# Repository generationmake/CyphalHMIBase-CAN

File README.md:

# CyphalHMIBase-CAN
HMI Board for the Raspberry Pi Pico with a display and some knobs to connect via CAN using OpenCyphal and UCANPHY Micro

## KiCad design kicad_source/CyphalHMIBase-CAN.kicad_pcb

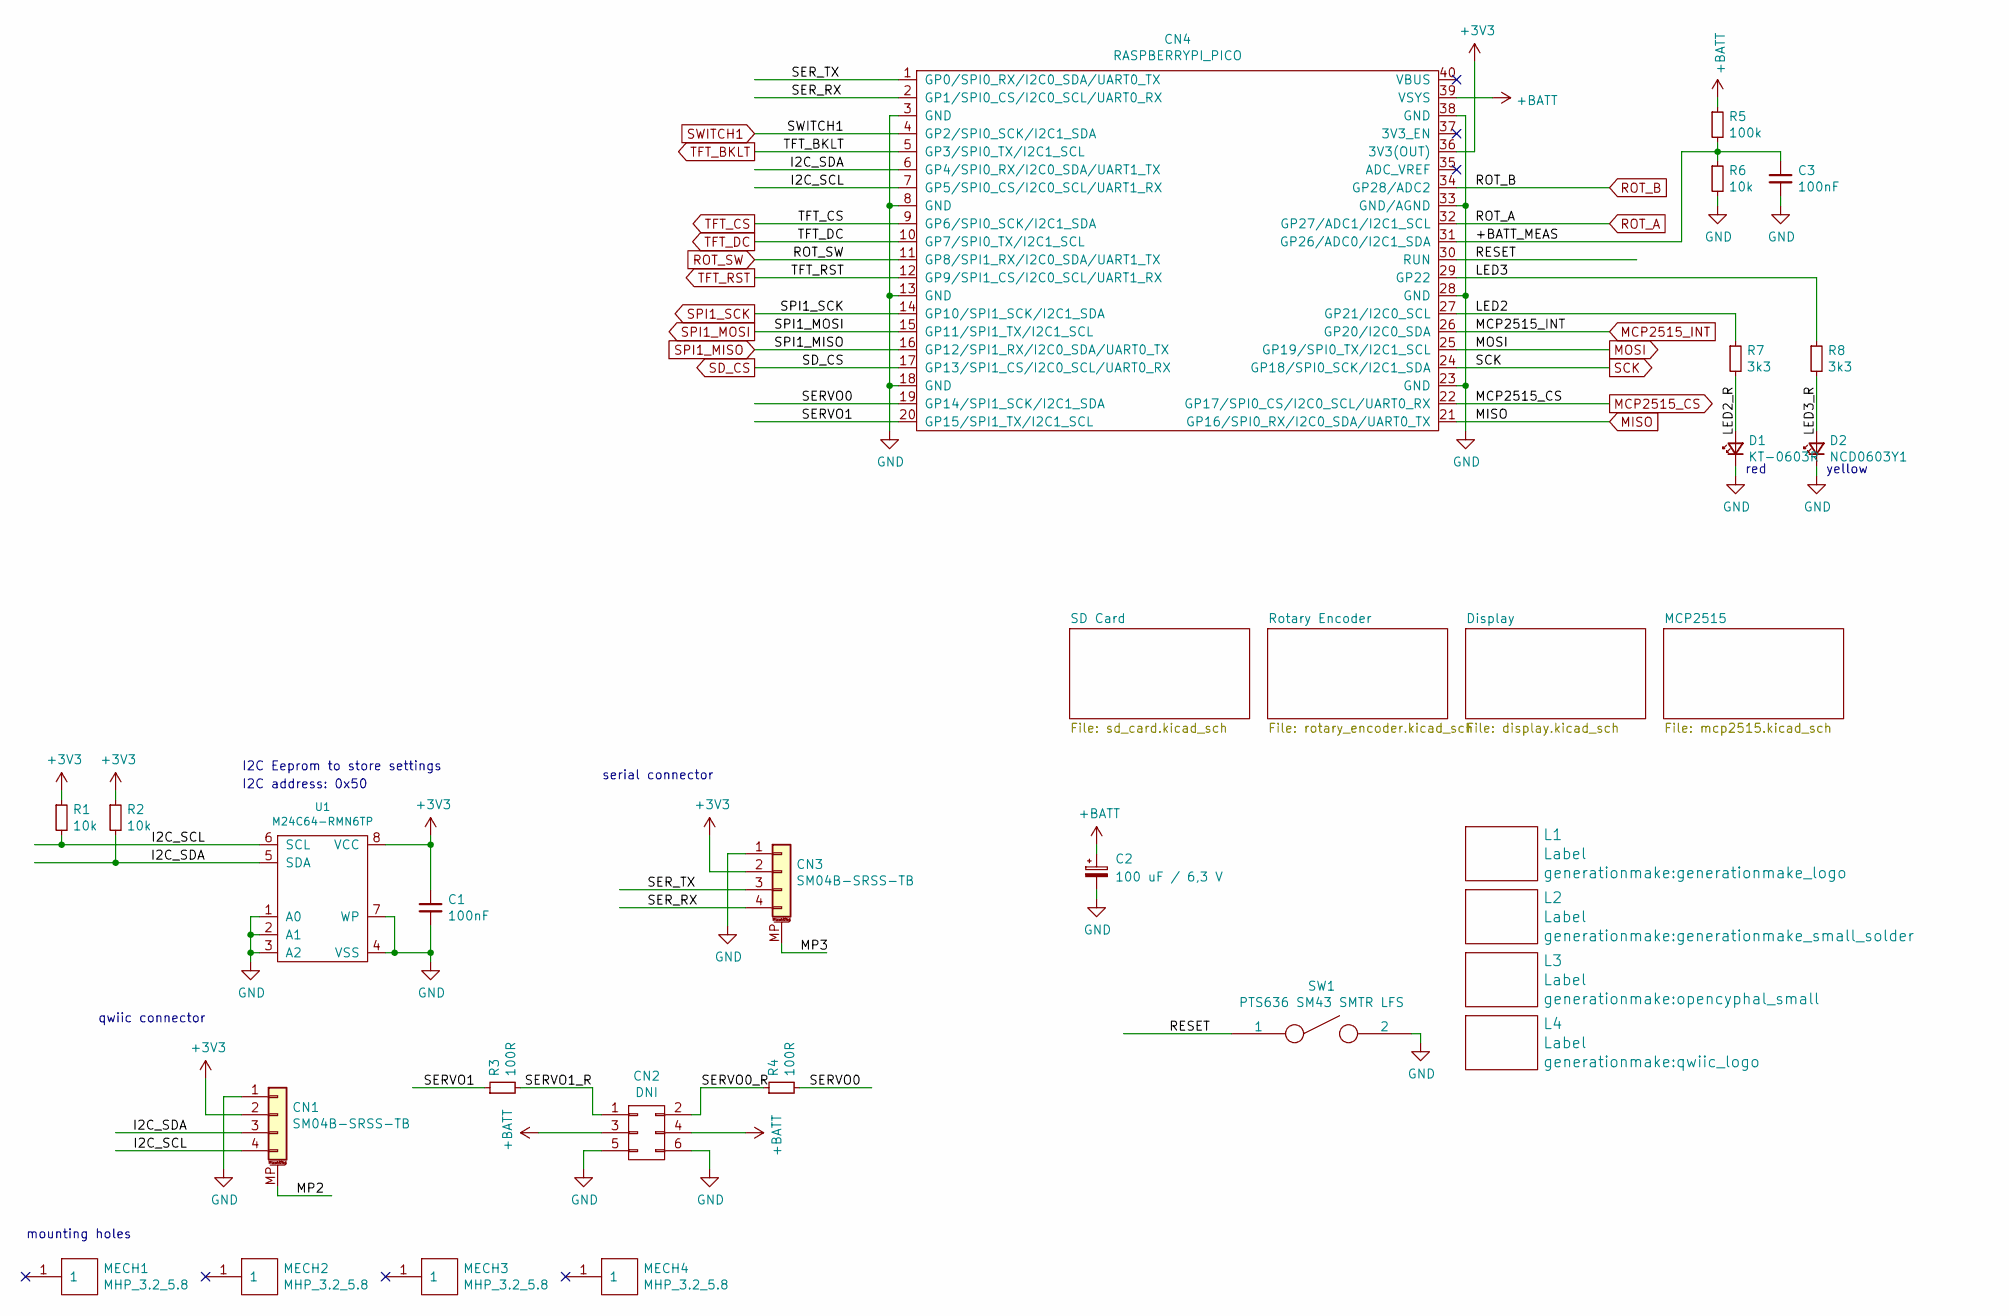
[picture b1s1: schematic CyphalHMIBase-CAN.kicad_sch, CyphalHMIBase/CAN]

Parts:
C1, C3: 100nF; C_0603_1608Metric; LCSC C14663
C2: 100 uF / 6,3 V; CP_Elec_5x5.3; LCSC C3001204
CN1, CN3: SM04B-SRSS-TB; JST_SH_SM04B-SRSS-TB_1x04-1MP_P1.00mm_Horizontal; LCSC C160404
CN2: DNI; PinHeader_2x03_P2.54mm_Horizontal
CN4: RASPBERRYPI_PICO; RASPI_PICO_SOLDER_ONLY
D1: KT-0603R; LED_0603_1608Metric; LCSC C2286
D2: NCD0603Y1; LED_0603_1608Metric; LCSC C84268
L1: Label; generationmake_logo
L2: Label; generationmake_small_solder
L3: Label; opencyphal_small
L4: Label; qwiic_logo
MECH1, MECH2, MECH3, MECH4: MHP_3.2_5.8
R1, R2, R6: 10k; R_0603_1608Metric; LCSC C25804
R3, R4: 100R; R_0603_1608Metric; LCSC C22775
R5: 100k; R_0603_1608Metric; LCSC C25803
R7, R8: 3k3; R_0603_1608Metric; LCSC C22978
SW1: PTS636 SM43 SMTR LFS; SW_SPST_CK_RS282G05A3; LCSC C2800965
U1: M24C64-RMN6TP; SOIC-8_3.9x4.9mm_P1.27mm; LCSC C79988

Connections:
+3V3: C1.1, CN1.2, CN3.2, CN4.36 (3V3(OUT)), R1.1, R2.1, U1.8 (VCC); also elsewhere on the board
+BATT: C2.1, CN2.3, CN2.4, CN4.39 (VSYS), R5.1; also elsewhere on the board
/+BATT_MEAS: C3.1, CN4.31 (GP26/ADC0/I2C1_SDA), R5.2, R6.1
/I2C_SCL: CN1.4, CN4.7 (GP5/SPI0_CS/I2C0_SCL/UART1_RX), R1.2, U1.6 (SCL)
/I2C_SDA: CN1.3, CN4.6 (GP4/SPI0_RX/I2C0_SDA/UART1_TX), R2.2, U1.5 (SDA)
/LED2: CN4.27 (GP21/I2C0_SCL), R7.1
/LED2_R: D1.2 (A), R7.2
/LED3: CN4.29 (GP22), R8.1
/LED3_R: D2.2 (A), R8.2
/MP2: CN1.MP (MountPin)
/MP3: CN3.MP (MountPin)
/RESET: CN4.30 (RUN), SW1.1
/SERVO0: CN4.19 (GP14/SPI1_SCK/I2C1_SDA), R4.2
/SERVO0_R: CN2.2, R4.1
/SERVO1: CN4.20 (GP15/SPI1_TX/I2C1_SCL), R3.1
/SERVO1_R: CN2.1, R3.2
/SER_RX: CN3.4, CN4.2 (GP1/SPI0_CS/I2C0_SCL/UART0_RX)
/SER_TX: CN3.3, CN4.1 (GP0/SPI0_RX/I2C0_SDA/UART0_TX)
GND: C1.2, C2.2, C3.2, CN1.1, CN2.5, CN2.6, CN3.1, CN4.3 (GND), CN4.8 (GND), CN4.13 (GND), CN4.18 (GND), CN4.23 (GND), CN4.28 (GND), CN4.33 (GND/AGND), CN4.38 (GND), D1.1 (K), D2.1 (K), R6.2, SW1.2, U1.1 (A0), U1.2 (A1), U1.3 (A2), U1.4 (VSS), U1.7 (WP); also elsewhere on the board
MCP2515_CS: CN4.22 (GP17/SPI0_CS/I2C0_SCL/UART0_RX); also elsewhere on the board
MCP2515_INT: CN4.26 (GP20/I2C0_SDA); also elsewhere on the board
MISO: CN4.21 (GP16/SPI0_RX/I2C0_SDA/UART0_TX); also elsewhere on the board
MOSI: CN4.25 (GP19/SPI0_TX/I2C1_SCL); also elsewhere on the board
ROT_A: CN4.32 (GP27/ADC1/I2C1_SCL); also elsewhere on the board
ROT_B: CN4.34 (GP28/ADC2); also elsewhere on the board
ROT_SW: CN4.11 (GP8/SPI1_RX/I2C0_SDA/UART1_TX); also elsewhere on the board
SCK: CN4.24 (GP18/SPI0_SCK/I2C1_SDA); also elsewhere on the board
SD_CS: CN4.17 (GP13/SPI1_CS/I2C0_SCL/UART0_RX); also elsewhere on the board
SPI1_MISO: CN4.16 (GP12/SPI1_RX/I2C0_SDA/UART0_TX); also elsewhere on the board
SPI1_MOSI: CN4.15 (GP11/SPI1_TX/I2C1_SCL); also elsewhere on the board
SPI1_SCK: CN4.14 (GP10/SPI1_SCK/I2C1_SDA); also elsewhere on the board
SWITCH1: CN4.4 (GP2/SPI0_SCK/I2C1_SDA); also elsewhere on the board
TFT_BKLT: CN4.5 (GP3/SPI0_TX/I2C1_SCL); also elsewhere on the board
TFT_CS: CN4.9 (GP6/SPI0_SCK/I2C1_SDA); also elsewhere on the board
TFT_DC: CN4.10 (GP7/SPI0_TX/I2C1_SCL); also elsewhere on the board
TFT_RST: CN4.12 (GP9/SPI1_CS/I2C0_SCL/UART1_RX); also elsewhere on the board

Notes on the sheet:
yellow
serial connector
qwiic connector
mounting holes
red
I2C address: 0x50
I2C Eeprom to store settings

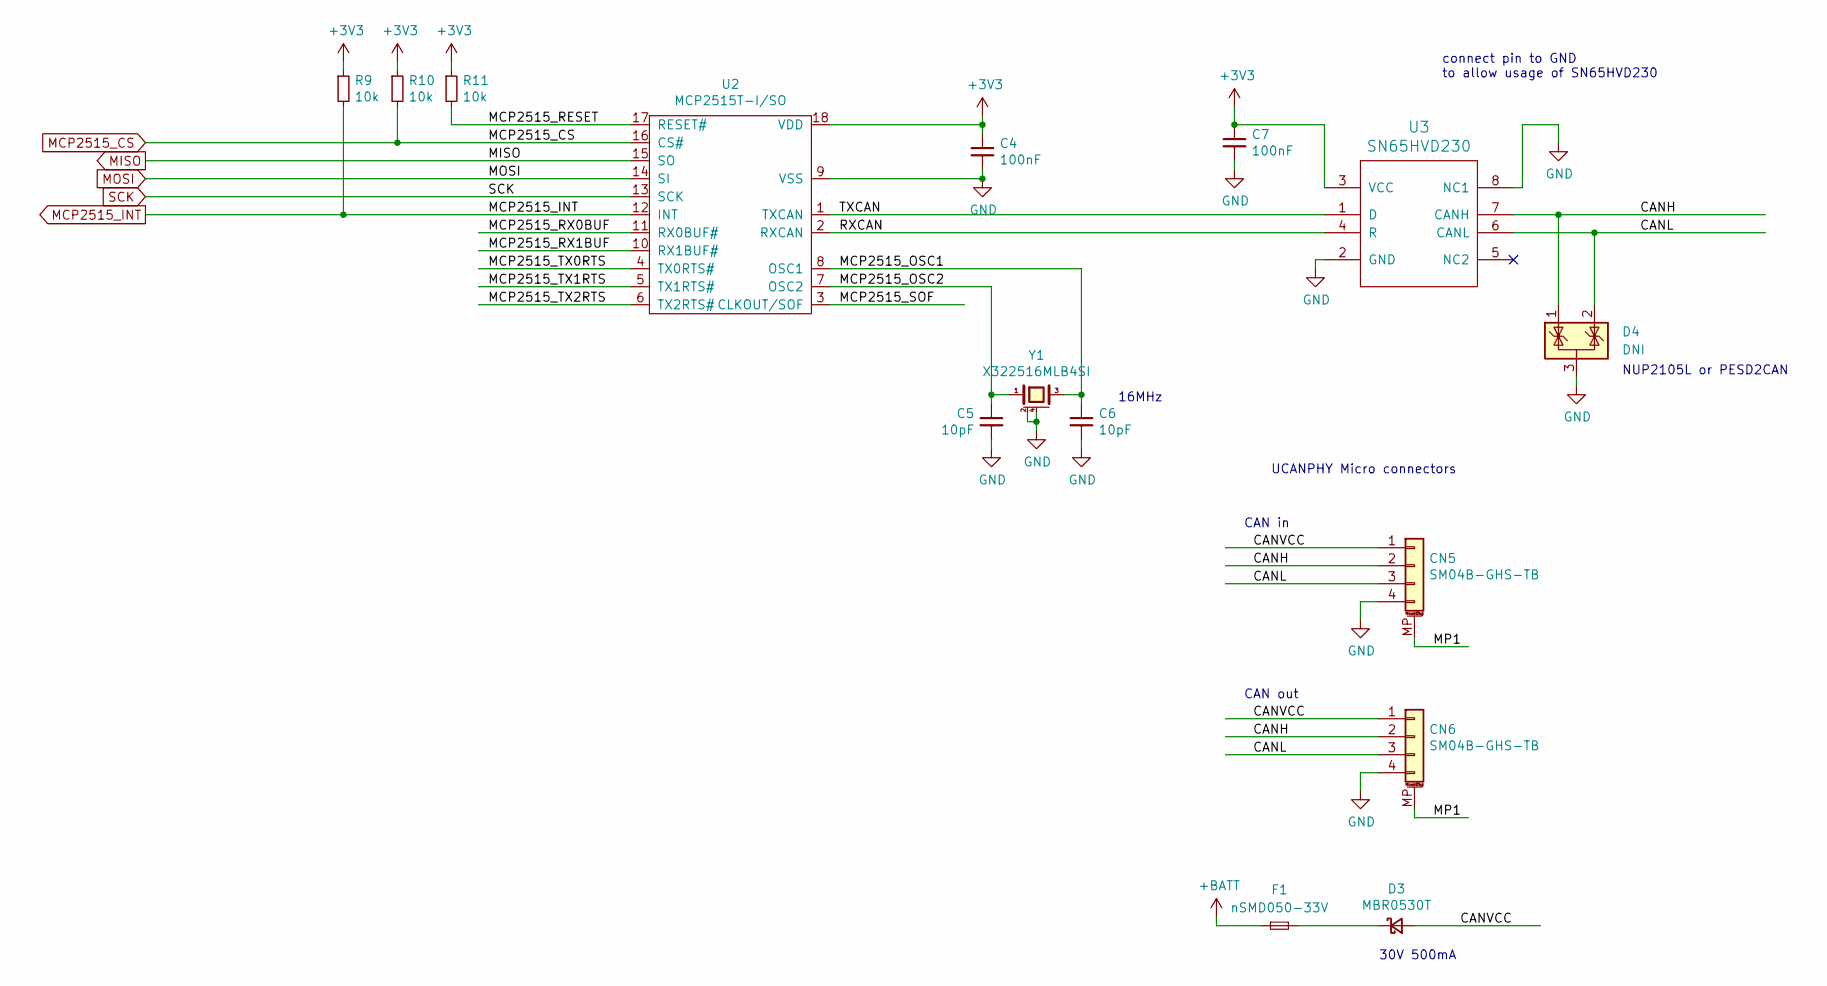
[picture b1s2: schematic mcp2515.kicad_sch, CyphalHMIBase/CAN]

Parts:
C4, C7: 100nF; C_0603_1608Metric; LCSC C14663
C5, C6: 10pF; C_0603_1608Metric; LCSC C1634
CN5, CN6: SM04B-GHS-TB; JST_GH_SM04B-GHS-TB_1x04-1MP_P1.25mm_Horizontal; LCSC C189895
D3: MBR0530T; D_SOD-123; LCSC C77336
D4: DNI; SOT-23
F1: nSMD050-33V; Fuse_1206_3216Metric; LCSC C70077
R9, R10, R11: 10k; R_0603_1608Metric; LCSC C25804
U2: MCP2515T-I/SO; SOIC-18W_7.5x11.6mm_P1.27mm; LCSC C153782
U3: SN65HVD230; SOIC-8_3.9x4.9mm_P1.27mm; LCSC C12084
Y1: X322516MLB4SI; Crystal_SMD_3.2x2.5mm_4Pad; LCSC C13738

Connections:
+3V3: C4.1, C7.1, R9.1, R10.1, R11.1, U2.18 (VDD), U3.3 (VCC); also elsewhere on the board
+BATT: F1.1; also elsewhere on the board
/MCP2515/CANH: CN5.2, CN6.2, D4.1 (K), U3.7 (CANH)
/MCP2515/CANL: CN5.3, CN6.3, D4.2 (K), U3.6 (CANL)
/MCP2515/CANVCC: CN5.1, CN6.1, D3.2 (A)
/MCP2515/MCP2515_OSC1: C6.1, U2.8 (OSC1), Y1.3
/MCP2515/MCP2515_OSC2: C5.1, U2.7 (OSC2), Y1.1
/MCP2515/MCP2515_RESET: R11.2, U2.17 (RESET#)
/MCP2515/MCP2515_RX0BUF: U2.11 (RX0BUF#)
/MCP2515/MCP2515_RX1BUF: U2.10 (RX1BUF#)
/MCP2515/MCP2515_SOF: U2.3 (CLKOUT/SOF)
/MCP2515/MCP2515_TX0RTS: U2.4 (TX0RTS#)
/MCP2515/MCP2515_TX1RTS: U2.5 (TX1RTS#)
/MCP2515/MCP2515_TX2RTS: U2.6 (TX2RTS#)
/MCP2515/MP1: CN5.MP (MountPin), CN6.MP (MountPin)
/MCP2515/RXCAN: U2.2 (RXCAN), U3.4 (R)
/MCP2515/TXCAN: U2.1 (TXCAN), U3.1 (D)
GND: C4.2, C5.2, C6.2, C7.2, CN5.4, CN6.4, D4.3 (A), U2.9 (VSS), U3.2 (GND), U3.8 (NC1), Y1.2 (case), Y1.4 (case); also elsewhere on the board
MCP2515_CS: R10.2, U2.16 (CS#); also elsewhere on the board
MCP2515_INT: R9.2, U2.12 (INT); also elsewhere on the board
MISO: U2.15 (SO); also elsewhere on the board
MOSI: U2.14 (SI); also elsewhere on the board
unnamed: D3.1 (K), F1.2
SCK: U2.13 (SCK); also elsewhere on the board

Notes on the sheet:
16MHz
NUP2105L or PESD2CAN
connect pin to GND to allow usage of SN65HVD230
UCANPHY Micro connectors
30V 500mA
CAN in
CAN out

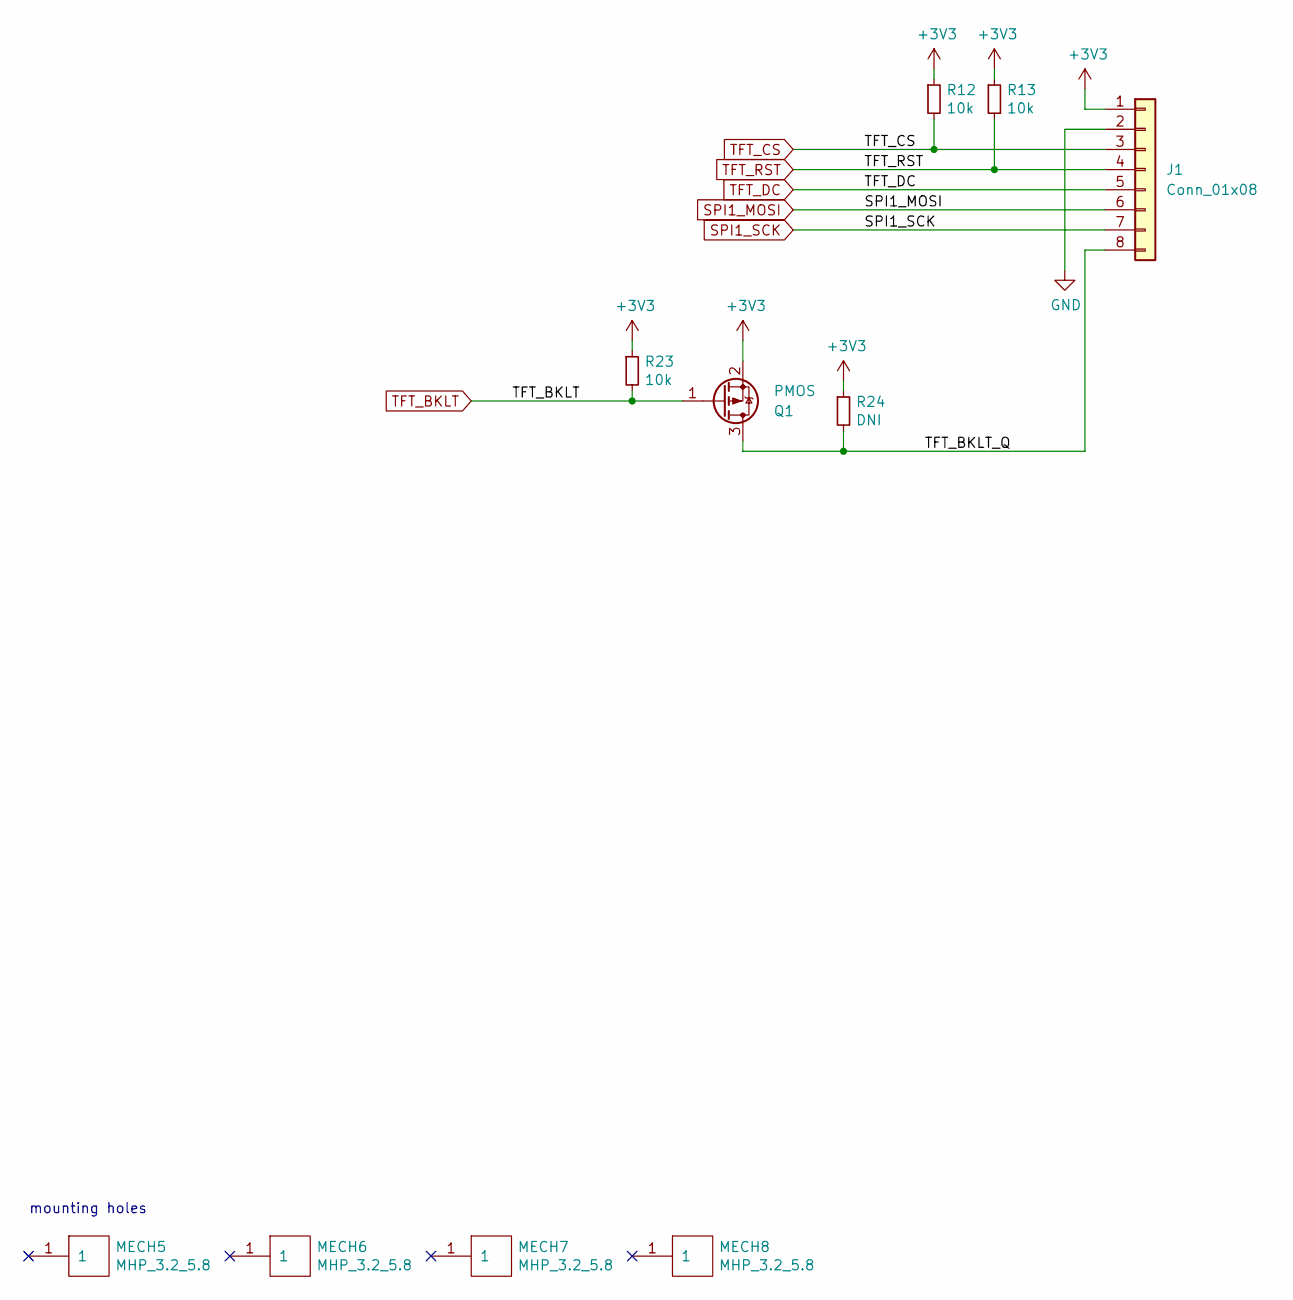
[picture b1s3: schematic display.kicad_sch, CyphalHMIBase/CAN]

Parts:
J1: Conn_01x08; PinHeader_1x08_P2.54mm_Vertical
MECH5, MECH6, MECH7, MECH8: MHP_3.2_5.8; MountingHole_3.2mm_M3_ISO14580_Pad
Q1: PMOS; SOT-23
R12, R13, R23: 10k; R_0603_1608Metric; LCSC C25804
R24: DNI; R_0603_1608Metric; LCSC C25804

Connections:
+3V3: J1.1, Q1.2 (S), R12.1, R13.1, R23.1, R24.1; also elsewhere on the board
/Display/TFT_BKLT_Q: J1.8, Q1.3 (D), R24.2
GND: J1.2; also elsewhere on the board
SPI1_MOSI: J1.6; also elsewhere on the board
SPI1_SCK: J1.7; also elsewhere on the board
TFT_BKLT: Q1.1 (G), R23.2; also elsewhere on the board
TFT_CS: J1.3, R12.2; also elsewhere on the board
TFT_DC: J1.5; also elsewhere on the board
TFT_RST: J1.4, R13.2; also elsewhere on the board

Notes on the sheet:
mounting holes

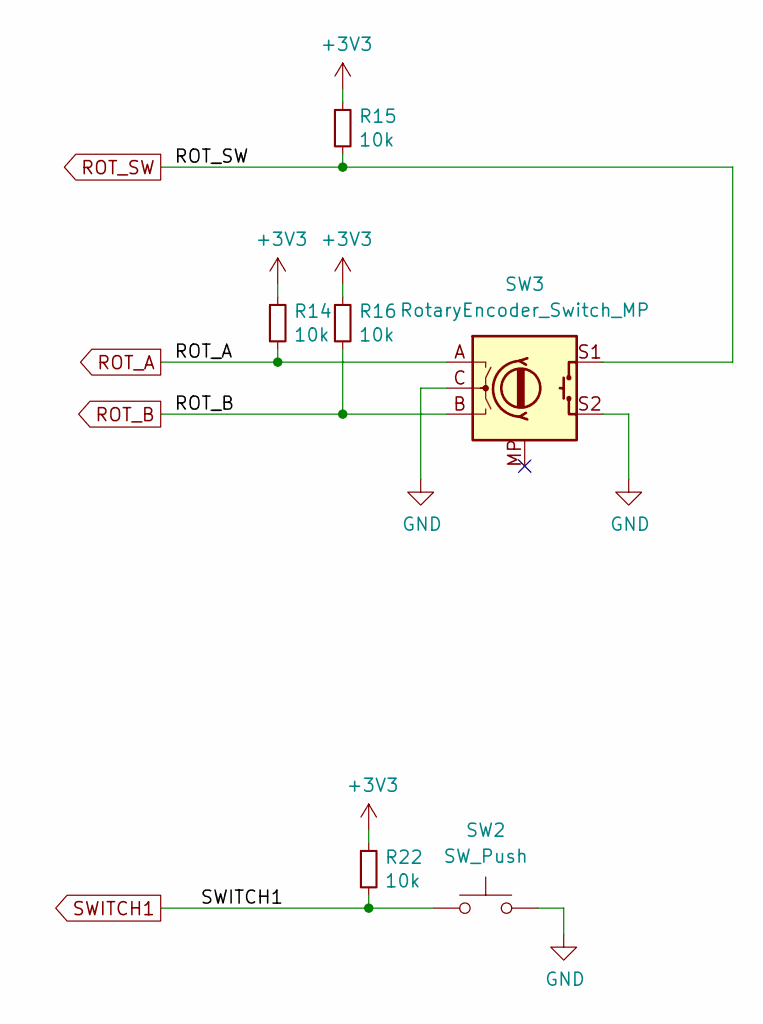
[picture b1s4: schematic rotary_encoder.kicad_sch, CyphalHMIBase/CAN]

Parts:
R14, R15, R16, R22: 10k; R_0603_1608Metric; LCSC C25804
SW2: SW_Push; SW_SPST_Omron_B3FS-100xP
SW3: RotaryEncoder_Switch_MP; RotaryEncoder_Alps_EC11E-Switch_Vertical_H20mm_CircularMoun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

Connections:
+3V3: R14.1, R15.1, R16.1, R22.1; also elsewhere on the board
GND: SW2.2, SW3.C, SW3.S2; also elsewhere on the board
ROT_A: R14.2, SW3.A; also elsewhere on the board
ROT_B: R16.2, SW3.B; also elsewhere on the board
ROT_SW: R15.2, SW3.S1; also elsewhere on the board
SWITCH1: R22.2, SW2.1; also elsewhere on the board

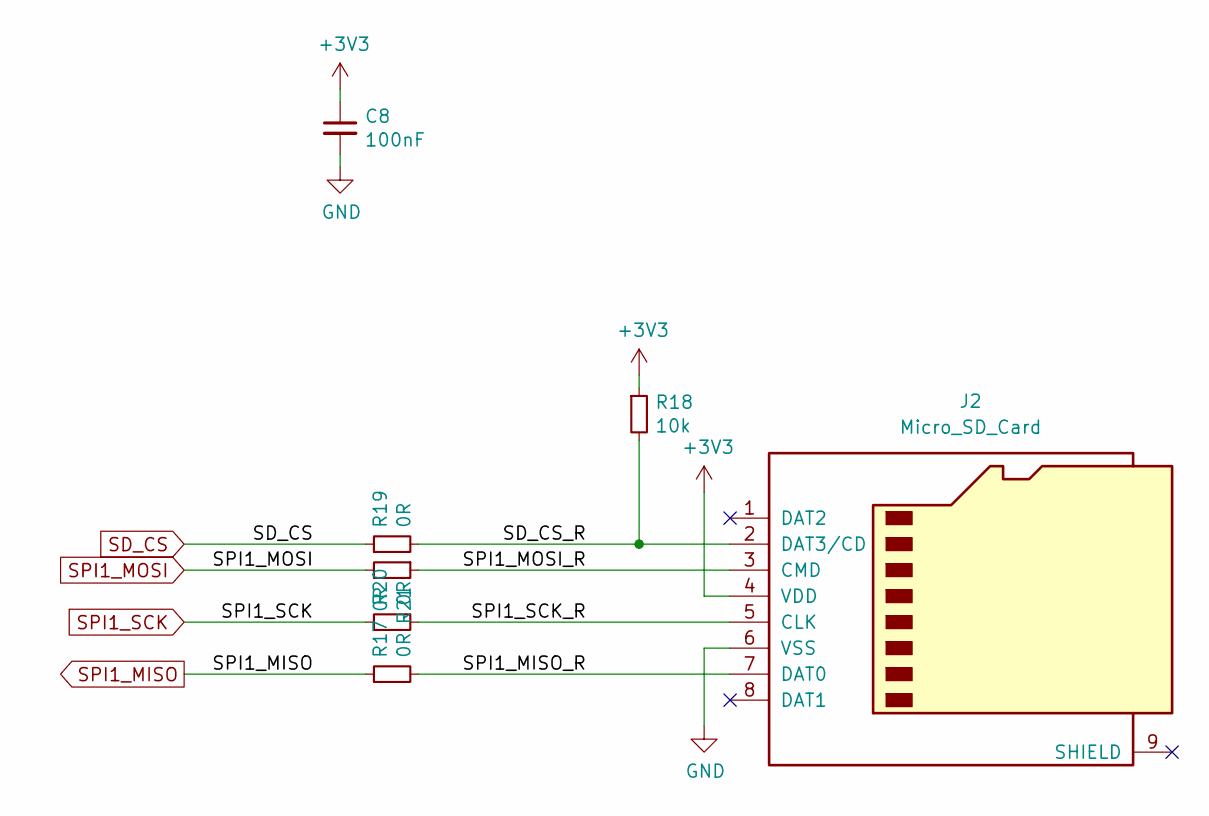
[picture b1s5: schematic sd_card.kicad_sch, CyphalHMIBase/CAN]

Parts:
C8: 100nF; C_0603_1608Metric; LCSC C14663
J2: Micro_SD_Card; WE_693071010811
R17, R19, R20, R21: 0R; R_0603_1608Metric; LCSC C22775
R18: 10k; R_0603_1608Metric; LCSC C25804

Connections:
+3V3: C8.1, J2.4 (VDD), R18.1; also elsewhere on the board
/SD Card/SD_CS_R: J2.2 (DAT3/CD), R18.2, R19.2
/SD Card/SPI1_MISO_R: J2.7 (DAT0), R17.2
/SD Card/SPI1_MOSI_R: J2.3 (CMD), R21.1
/SD Card/SPI1_SCK_R: J2.5 (CLK), R20.2
GND: C8.2, J2.6 (VSS); also elsewhere on the board
SD_CS: R19.1; also elsewhere on the board
SPI1_MISO: R17.1; also elsewhere on the board
SPI1_MOSI: R21.2; also elsewhere on the board
SPI1_SCK: R20.1; also elsewhere on the board

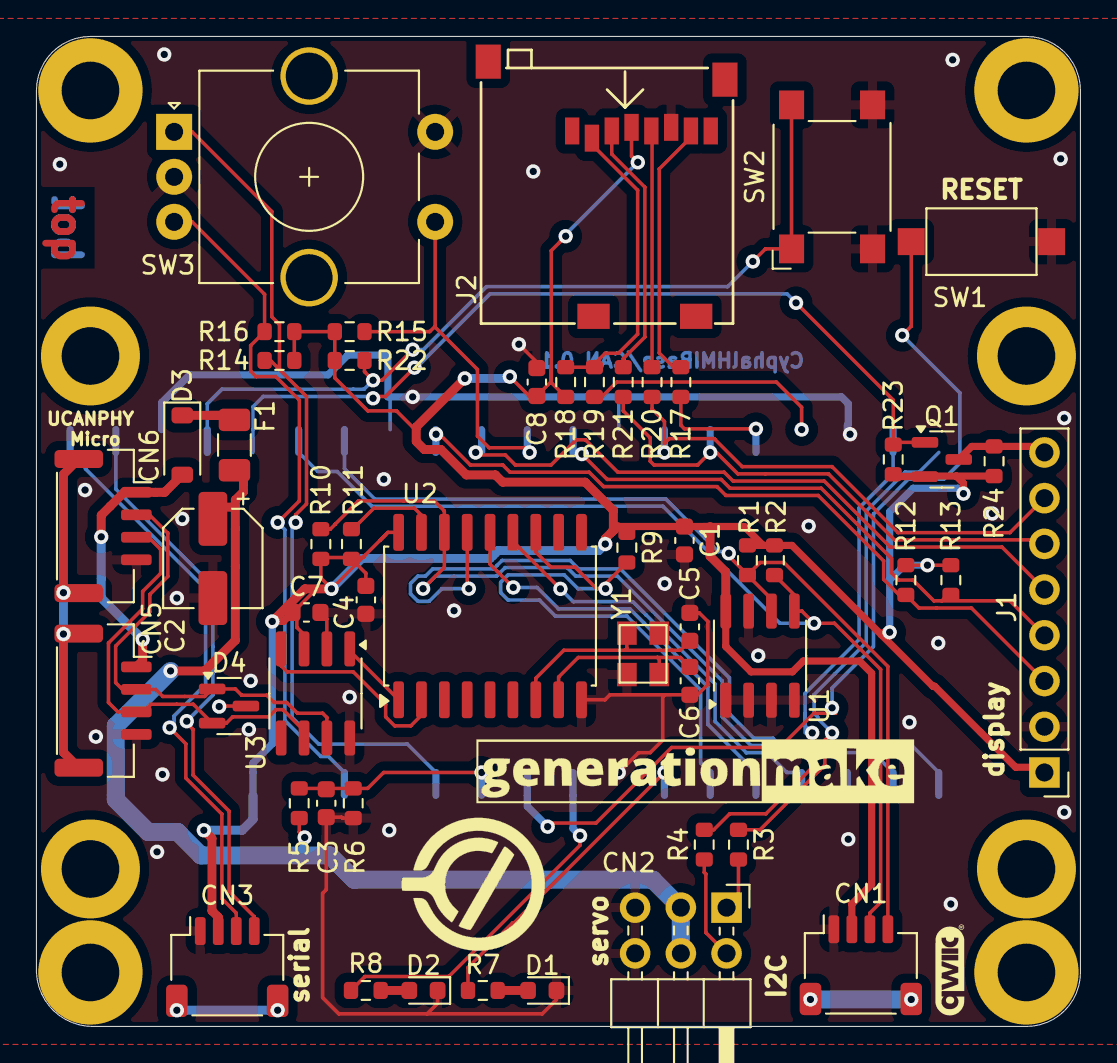
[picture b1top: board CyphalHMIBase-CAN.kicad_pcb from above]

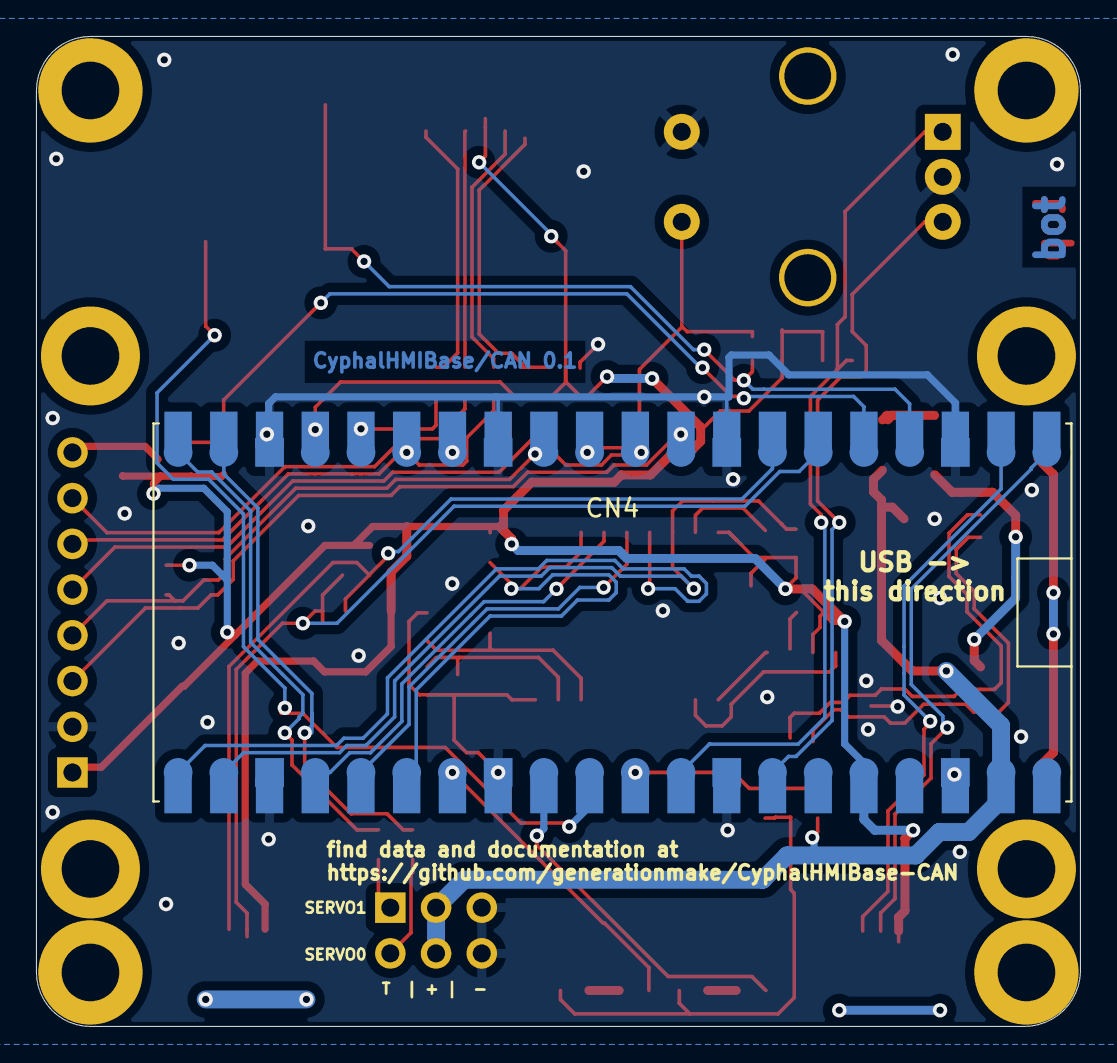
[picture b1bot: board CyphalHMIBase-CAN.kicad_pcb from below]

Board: 2 copper layers, 58.0 x 55.0 mm, 65 parts (2 on the bottom side), 49 nets.

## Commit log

2026-06-03 copied files from CyphalPicoBase/CAN
2026-06-03 removed unnecessary parts
2026-06-03 added display
2026-06-03 added display schematic page
2026-06-04 added encoder, mounting holes for display at correct position
2026-06-05 added sd card, updated layout
2026-06-05 added push button
2026-06-05 added backlight control
2026-06-05 added schematic pdf
2026-06-06 fixed drc errors
2026-06-08 fixed micro sd card connector
